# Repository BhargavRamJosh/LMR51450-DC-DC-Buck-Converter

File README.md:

# LMR51450 DC-DC Buck Converter
DC-DC Buck Converter using TI LMR51450, input 10–35V, output 7.6V 4A. Designed in KiCad

---

## 📌 Overview
This project implements a **DC-DC Buck Converter** based on the **Texas Instruments LMR51450**.  
It is designed in **KiCad** with the following specifications:

- **Input Voltage:** 10 V – 35 V  
- **Output Voltage:** 7.6 V  
- **Output Current:** 4 A  
- **Switching Frequency:** 500 kHz (default, RT pin open)  

The design includes proper **input/output filtering**, **optimized trace widths**, and follows **PCB routing guidelines** for stable performance.

---

## 📂 Repository Structure
- `Task1_buck_converter/Schematics/` → KiCad schematic files (`.kicad_sch`, `.kicad_pro`)  
- `Task1_buck_converter/PCB/` → PCB layout file (`.kicad_pcb`)  
- `Task1_buck_converter/BOM/` → Bill of Materials (`.csv`)  
- `MEDIA/` → Snapshots of schematic & PCB (`.png`)  

---

## 📷 Design Media

### 🔹 Full Design Block Diagram

### 🔹 Complete Schematic

### 🔹 PCB Routing Layout

---

## 🛠 Tools Used
- **KiCad 7/8** → Schematic & PCB design  
- **BOM Generator** → CSV output  
- **GitHub** → Version control & project hosting  

---

## 🔧 Design Specifications
- **Input Voltage Range:** 10V – 35V DC  
- **Output Voltage:** 7.6V DC  
- **Maximum Output Current:** 4A  
- **Switching Frequency:** 500 kHz  
- **Efficiency:** >90% at full load  

---

---

## 🚀 Getting Started
Clone this repository:
```bash
git clone https://github.com/your-username/LMR51450-DC-DC-Buck-Converter.git

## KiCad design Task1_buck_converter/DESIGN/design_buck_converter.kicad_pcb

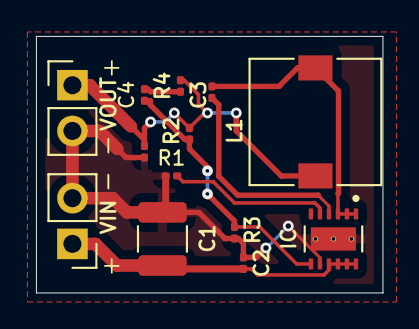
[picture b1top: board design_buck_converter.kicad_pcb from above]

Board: 2 copper layers, 19.2 x 14.2 mm, 13 parts (0 on the bottom side), 8 nets.

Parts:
C1: 10uF; C_1210_3225Metric
C2, C3: 0.1uF; C_0201_0603Metric
C4: 33pF; C_0201_0603Metric
C5: 47uF; C_0201_0603Metric
IC: LMR51450SDRRR; CONV_LMR51450SDRRR
L1: 10uH; L_SXN_SMDRI62
R1, R3: 10K; R_0201_0603Metric
R2: 85K; R_0201_0603Metric
R4: 1K; R_0201_0603Metric
VIN: VIN; PinHeader_1x02_P2.54mm_Vertical
VOUT: VOUT; PinHeader_1x02_P2.54mm_Vertical

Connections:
GND: C1.2, C2.2, C5.2, IC.8 (AGND), IC.13 (PGND), IC.14, IC.15, IC.16, R1.2, R3.2, VIN.2, VOUT.2
unnamed: C3.2, IC.1 (SW), IC.2 (SW), IC.3 (SW), L1.1
unnamed: C4.1, R4.2
unnamed: C1.1, C2.1, IC.9 (EN), IC.10 (VIN), IC.11 (VIN), IC.12 (VIN), VIN.1
unnamed: C5.1, L1.2, R2.1, R4.1, VOUT.1
unnamed: C3.1, IC.4 (BOOT)
unnamed: C4.2, IC.7 (FB), R2.2, R3.1
unnamed: IC.5 (PG), R1.1
